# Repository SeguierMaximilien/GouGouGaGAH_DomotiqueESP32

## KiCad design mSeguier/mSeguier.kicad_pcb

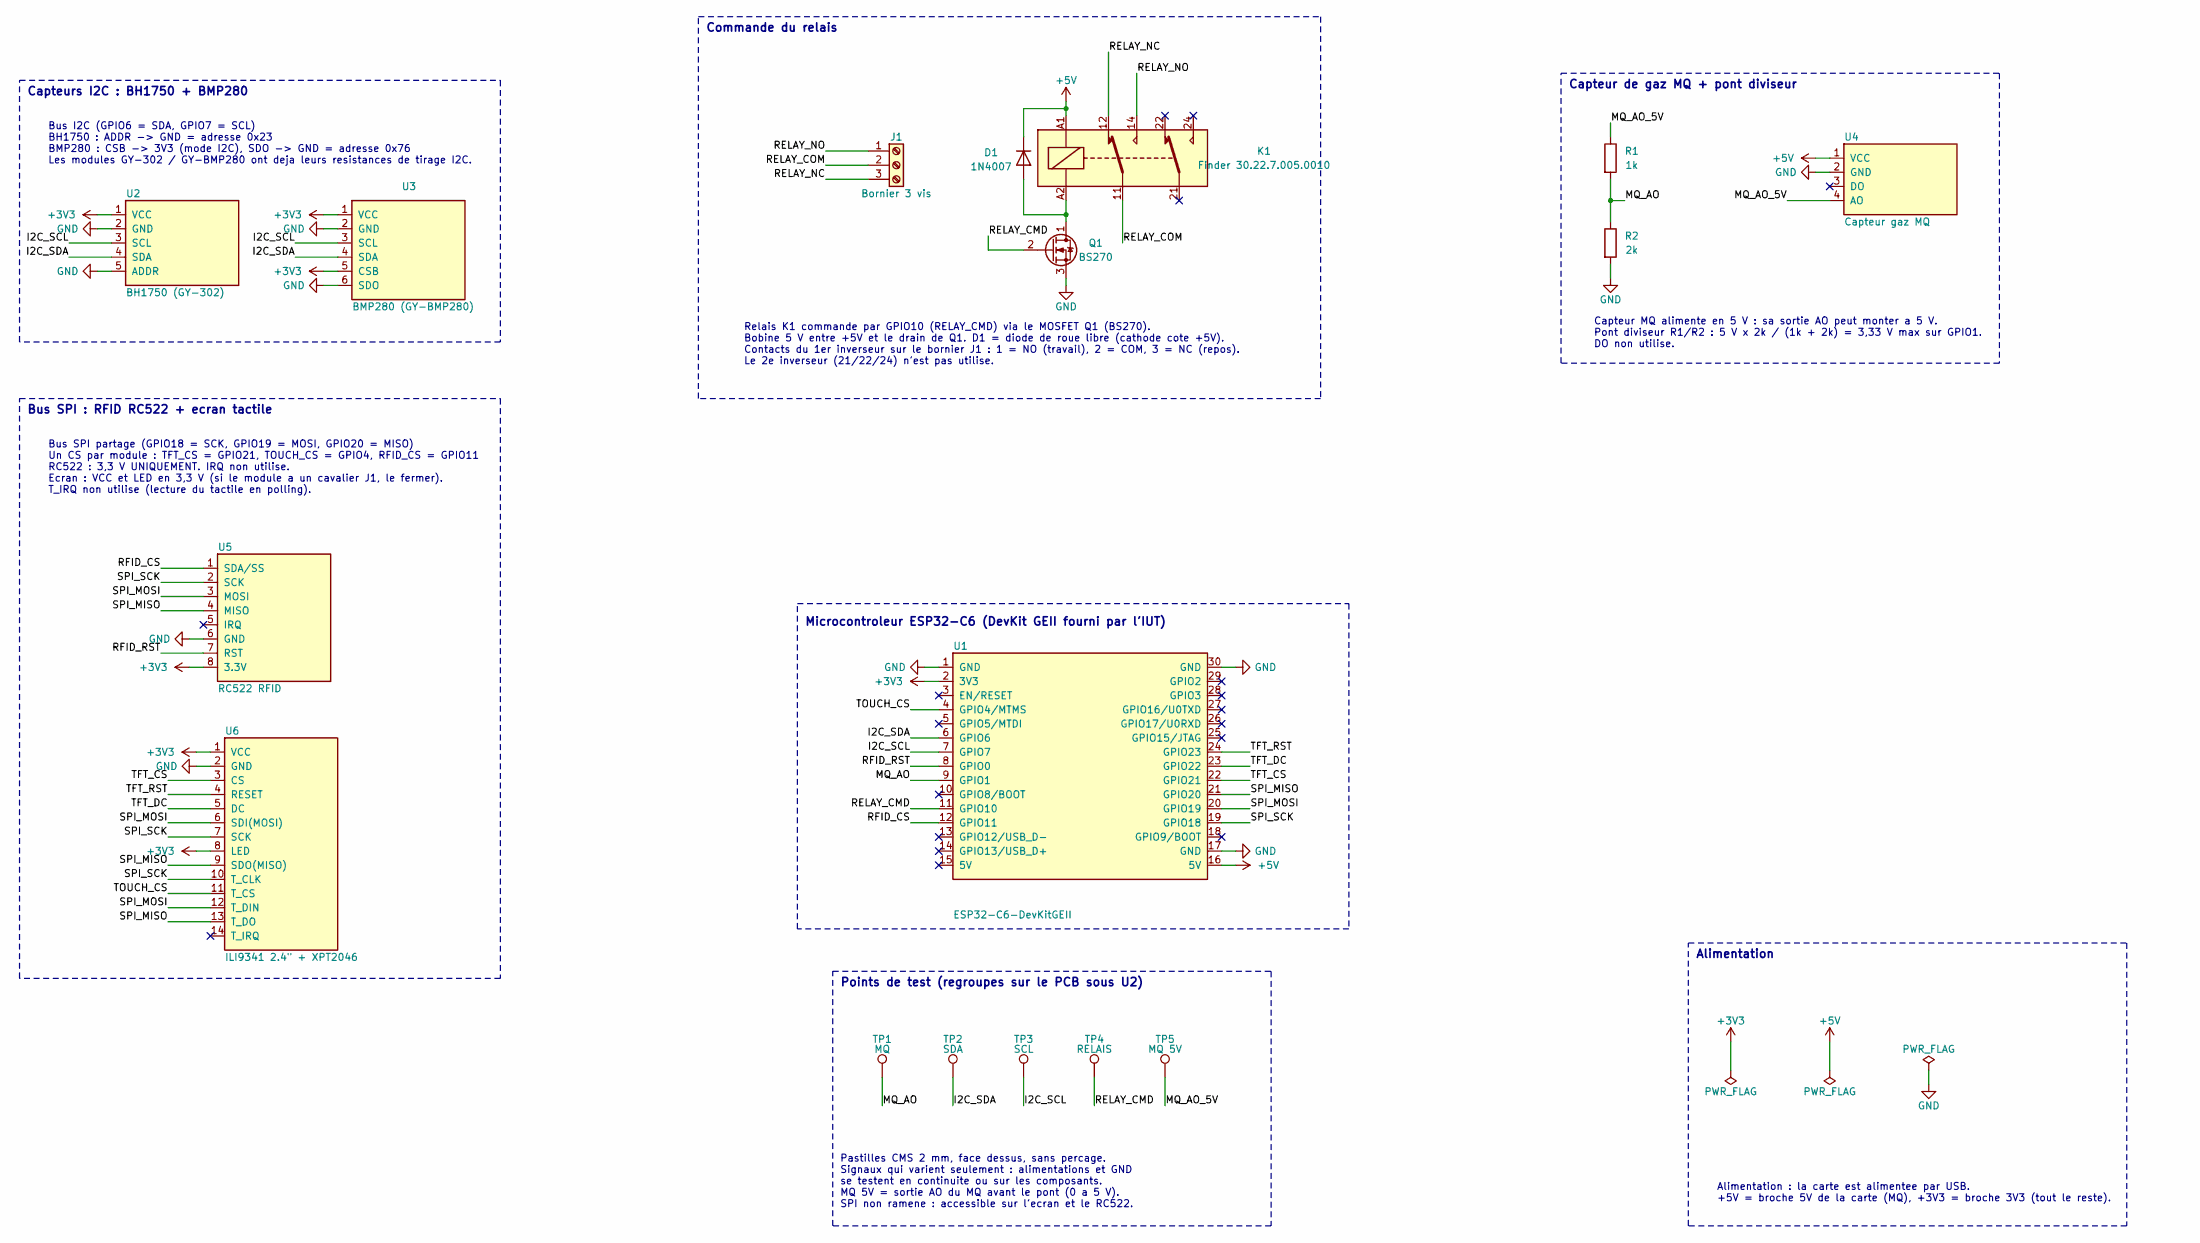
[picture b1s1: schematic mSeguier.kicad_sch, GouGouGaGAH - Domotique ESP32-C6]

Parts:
D1: 1N4007; D_DO-41_SOD81_P10.16mm_Horizontal
J1: Bornier 3 vis; TerminalBlock_Phoenix_MKDS-1,5-3_1x03_P5.00mm_Horizontal
K1: Finder 30.22.7.005.0010; Relay_DPDT_Finder_30.22
Q1: BS270; TO-92_Inline_Wide
R1: 1k; R_Axial_DIN0207_L6.3mm_D2.5mm_P10.16mm_Horizontal
R2: 2k; R_Axial_DIN0207_L6.3mm_D2.5mm_P10.16mm_Horizontal
TP1: MQ; TestPoint_Pad_D2.0mm
TP2: SDA; TestPoint_Pad_D2.0mm
TP3: SCL; TestPoint_Pad_D2.0mm
TP4: RELAIS; TestPoint_Pad_D2.0mm
TP5: MQ 5V; TestPoint_Pad_D2.0mm
U1: ESP32-C6-DevKitGEII
U2: BH1750 (GY-302); BH1750_GY-302
U3: BMP280 (GY-BMP280); BMP280_GY-BMP280-3.3
U4: Capteur gaz MQ; MQ_Gas_Sensor_Module_FlyingFish
U5: RC522 RFID; RFID_RC522_Module
U6: ILI9341 2.4" + XPT2046; TFT_2.4in_SPI_ILI9341_MSP2402

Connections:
+3V3: U1.2 (3V3), U2.1 (VCC), U3.1 (VCC), U3.5 (CSB), U5.8 (3.3V), U6.1 (VCC), U6.8 (LED)
+5V: D1.1 (K), K1.A1, U1.16 (5V), U4.1 (VCC)
/I2C_SCL: TP3.1, U1.7 (GPIO7), U2.3 (SCL), U3.3 (SCL)
/I2C_SDA: TP2.1, U1.6 (GPIO6), U2.4 (SDA), U3.4 (SDA)
/MQ_AO: R1.2, R2.1, TP1.1, U1.9 (GPIO1)
/MQ_AO_5V: R1.1, TP5.1, U4.4 (AO)
/RELAY_CMD: Q1.2 (G), TP4.1, U1.11 (GPIO10)
/RELAY_COM: J1.2, K1.11
/RELAY_NC: J1.3, K1.12
/RELAY_NO: J1.1, K1.14
/RFID_CS: U1.12 (GPIO11), U5.1 (SDA/SS)
/RFID_RST: U1.8 (GPIO0), U5.7 (RST)
/SPI_MISO: U1.21 (GPIO20), U5.4 (MISO), U6.9 (SDO(MISO)), U6.13 (T_DO)
/SPI_MOSI: U1.20 (GPIO19), U5.3 (MOSI), U6.6 (SDI(MOSI)), U6.12 (T_DIN)
/SPI_SCK: U1.19 (GPIO18), U5.2 (SCK), U6.7 (SCK), U6.10 (T_CLK)
/TFT_CS: U1.22 (GPIO21), U6.3 (CS)
/TFT_DC: U1.23 (GPIO22), U6.5 (DC)
/TFT_RST: U1.24 (GPIO23), U6.4 (RESET)
/TOUCH_CS: U1.4 (GPIO4/MTMS), U6.11 (T_CS)
GND: Q1.3 (S), R2.2, U1.1 (GND), U1.17 (GND), U1.30 (GND), U2.2 (GND), U2.5 (ADDR), U3.2 (GND), U3.6 (SDO), U4.2 (GND), U5.6 (GND), U6.2 (GND)
unnamed: D1.2 (A), K1.A2, Q1.1 (D)

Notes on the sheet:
Capteur de gaz MQ + pont diviseur
Bus SPI : RFID RC522 + ecran tactile
Bus SPI partage (GPIO18 = SCK, GPIO19 = MOSI, GPIO20 = MISO) Un CS par module : TFT_CS = GPIO21, TOUCH_CS = GPIO4, RFID_CS = GPIO11 RC522 : 3,3 V UNIQUEMENT. IRQ non utilise. Ecran : VCC et LED en 3,3 V (si le module a un cavalier J1, le fermer). T_IRQ non utilise (lecture du tactile en polling).
Capteurs I2C : BH1750 + BMP280
Commande du relais
Alimentation
Relais K1 commande par GPIO10 (RELAY_CMD) via le MOSFET Q1 (BS270). Bobine 5 V entre +5V et le drain de Q1. D1 = diode de roue libre (cathode cote +5V). Contacts du 1er inverseur sur le bornier J1 : 1 = NO (travail), 2 = COM, 3 = NC (repos). Le 2e inverseur (21/22/24) n'est pas utilise.
Alimentation : la carte est alimentee par USB. +5V = broche 5V de la carte (MQ), +3V3 = broche 3V3 (tout le reste).
Microcontroleur ESP32-C6 (DevKit GEII fourni par l'IUT)
Capteur MQ alimente en 5 V : sa sortie AO peut monter a 5 V. Pont diviseur R1/R2 : 5 V x 2k / (1k + 2k) = 3,33 V max sur GPIO1. DO non utilise.
Bus I2C (GPIO6 = SDA, GPIO7 = SCL) BH1750 : ADDR -> GND = adresse 0x23 BMP280 : CSB -> 3V3 (mode I2C), SDO -> GND = adresse 0x76 Les modules GY-302 / GY-BMP280 ont deja leurs resistances de tirage I2C.
Points de test (regroupes sur le PCB sous U2)
Pastilles CMS 2 mm, face dessus, sans percage. Signaux qui varient seulement : alimentations et GND se testent en continuite ou sur les composants. MQ 5V = sortie AO du MQ avant le pont (0 a 5 V). SPI non ramene : accessible sur l'ecran et le RC522.

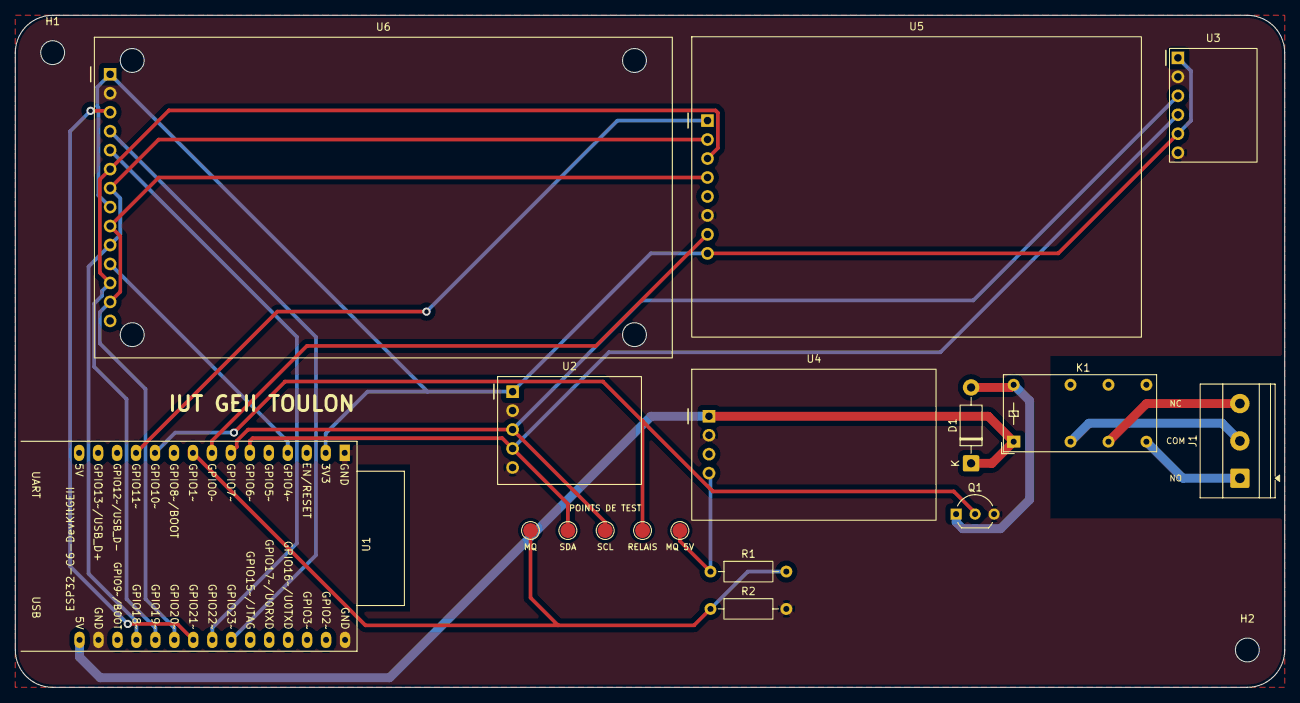
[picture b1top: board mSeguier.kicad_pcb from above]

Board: 2 copper layers, 170.0 x 90.0 mm, 19 parts (0 on the bottom side), 21 nets.

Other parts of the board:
H1, H2: M3; MountingHole_3.2mm_M3

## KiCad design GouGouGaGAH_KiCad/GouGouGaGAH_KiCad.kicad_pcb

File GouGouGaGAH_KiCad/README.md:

# GouGouGaGAH_KiCad : schéma du projet domotique

Sous-projet KiCad du montage ESP32-C6. Le schéma reprend exactement le brochage de
`GouGouGaGAH_DomotiqueESP32/include/pinout.h`.

## Ouvrir le projet

1. Ouvre `GouGouGaGAH_KiCad.kicad_pro` avec KiCad (version 8, 9 ou 10).
2. Ouvre le schéma : tout est déjà relié et chaque composant a son empreinte.
3. Le circuit imprimé (`GouGouGaGAH_KiCad.kicad_pcb`) est placé et routé (voir plus bas).
   Si tu modifies le schéma, mets le PCB à jour avec *Outils > Mettre à jour le PCB depuis le
   schéma* (touche F8).

Le dossier contient sa propre bibliothèque, déclarée dans les tables du projet :

| Fichier | Contenu |
|---|---|
| `GouGouGaGAH.kicad_sym` | Symboles de la carte nanoESP32-C6 et des 5 modules (plus la DevKitC-1 en réserve) |
| `../Kad_Lib/ESP32_C6_modules.pretty/` | Tes empreintes : carte et 5 modules |
| `GouGouGaGAH.pretty/` | Empreinte ESP32-C6-DevKitC-1 (en réserve, non utilisée) |
| `sym-lib-table`, `fp-lib-table` | Déclarent ces bibliothèques pour ce projet uniquement |

Les résistances et condensateurs utilisent les bibliothèques standard de KiCad.
Garde le dossier `Kad_Lib` à côté de `GouGouGaGAH_KiCad`, le chemin est relatif.

## Circuit imprimé

- Carte double face de 165 × 114 mm, aperçus dans `rendu_pcb.png` (dessus) et `rendu_pcb_dessous.png`.
- GND : aucune piste, tout passe par un plan de masse sur les deux faces (rayons thermiques
  pour faciliter la soudure, liaison pleine sur U2 broche 2 et Q1 broche 3).
- Haut : écran (gauche) et RC522 (droite). Milieu : nanoESP32-C6 avec l'USB-C au bord gauche,
  BH1750 et BMP280 à côté. Bas : capteur MQ, pont R1/R2/C1, condensateurs C2/C3.
  À droite : relais, MOSFET, diode et bornier au bord de la carte.
- Les modules s'enfichent sur des barrettes : des pistes passent sous les modules, c'est normal.
  Aucune piste sous l'antenne de la nanoESP32-C6 (zone interdite de l'empreinte).
- Largeurs : 0,3 mm pour les signaux, 0,8 mm pour +5V / +3V3 / bobine du relais,
  1,5 mm pour les contacts du relais. Isolement 0,2 mm (0,5 mm pour les contacts du relais).
- Contrôle KiCad (DRC) : 0 erreur, 0 avertissement, 0 liaison manquante, PCB conforme au schéma.
- Si tu modifies des pistes, refais le remplissage des plans avec la touche B.
- **Attention** : les contacts du relais ne sont pas isolés pour du 230 V (il faudrait
  plusieurs millimètres d'écart et une fente). Ne commute que de la basse tension avec cette carte.

## Liaisons

| Réseau | ESP32-C6 | Relié à |
|---|---|---|
| I2C_SDA | GPIO6 | BH1750 SDA, BMP280 SDA |
| I2C_SCL | GPIO7 | BH1750 SCL, BMP280 SCL |
| SPI_SCK | GPIO18 | RC522 SCK, écran SCK, tactile T_CLK |
| SPI_MOSI | GPIO19 | RC522 MOSI, écran SDI, tactile T_DIN |
| SPI_MISO | GPIO20 | RC522 MISO, écran SDO, tactile T_DO |
| TFT_CS | GPIO21 | écran CS |
| TFT_DC | GPIO22 | écran DC |
| TFT_RST | GPIO23 | écran RESET |
| TOUCH_CS | GPIO4 | tactile T_CS |
| RFID_CS | GPIO11 | RC522 SDA/SS |
| RFID_RST | GPIO0 | RC522 RST |
| MQ_AO | GPIO1 | point milieu du pont R1/R2 (+ C1) |
| MQ_AO_5V | - | sortie AO du capteur MQ, entrée du pont R1/R2 |
| RELAY_CMD | GPIO10 | grille du MOSFET Q1 |
| RELAY_COIL | - | drain de Q1, bobine A2 du relais, anode de D1 |
| RELAY_NO / COM / NC | - | contacts 14 / 11 / 12 du relais, vers le bornier J1 (1 / 2 / 3) |
| +5V | broches 5V | capteur MQ (VCC), bobine A1 du relais, cathode de D1 |
| +3V3 | broche 3V3 | BH1750, BMP280 (VCC + CSB), RC522, écran (VCC + LED) |
| GND | GND | tout le monde, plus BH1750 ADDR et BMP280 SDO |

Broches non utilisées (croix « non connecté ») : MQ DO, RC522 IRQ, écran T_IRQ, et les GPIO libres de la carte.

## Composants et empreintes

| Réf. | Composant | Empreinte |
|---|---|---|
| U1 | MuseLab nanoESP32-C6 (2 x 15 broches) | `ESP32_C6_modules:MuseLab_nanoESP32-C6` |
| U2 | BH1750 (GY-302) | `ESP32_C6_modules:BH1750_GY-302` |
| U3 | BMP280 (GY-BMP280) | `ESP32_C6_modules:BMP280_GY-BMP280-3.3` |
| U4 | Capteur gaz MQ | `ESP32_C6_modules:MQ_Gas_Sensor_Module_FlyingFish` |
| U5 | RC522 | `ESP32_C6_modules:RFID_RC522_Module` |
| U6 | Écran ILI9341 2.4" + XPT2046 (MSP2402) | `ESP32_C6_modules:TFT_2.4in_SPI_ILI9341_MSP2402` |
| R1 | 1 kΩ | `Resistor_THT:R_Axial_DIN0207_L6.3mm_D2.5mm_P10.16mm_Horizontal` |
| R2 | 2 kΩ | `Resistor_THT:R_Axial_DIN0207_L6.3mm_D2.5mm_P10.16mm_Horizontal` |
| C1 | 100 nF | `Capacitor_THT:C_Disc_D5.0mm_W2.5mm_P5.00mm` |
| C2 | 10 µF (sur +3V3) | `Capacitor_THT:CP_Radial_D5.0mm_P2.00mm` |
| C3 | 10 µF (sur +5V) | `Capacitor_THT:CP_Radial_D5.0mm_P2.00mm` |
| Q1 | MOSFET BS270 (symbole BS170, même brochage D-G-S) | `Package_TO_SOT_THT:TO-92_Inline` |
| K1 | Relais Finder 30.22.7.005 (2 inverseurs, bobine 5 V) | `Relay_THT:Relay_DPDT_Finder_30.22` |
| D1 | Diode de roue libre 1N4007 | `Diode_THT:D_DO-41_SOD81_P10.16mm_Horizontal` |
| J1 | Bornier à vis 3 points, pas de 5 mm | `TerminalBlock_Phoenix:TerminalBlock_Phoenix_MKDS-1,5-3_1x03_P5.00mm_Horizontal` |

L'ordre des broches des symboles est identique à celui de tes empreintes (vérifié broche par broche).
Sur l'empreinte de la nanoESP32-C6, les textes de sérigraphie des broches 7 à 15 et 22 à 30 sont
décalés par rapport aux pastilles : la numérotation reste juste, c'est seulement l'affichage.

## Points d'attention

- **Capteur MQ** : alimenté en 5 V, sa sortie AO peut monter à 5 V alors que l'ESP32 n'accepte
  que 3,3 V. Le pont R1 (1 kΩ) / R2 (2 kΩ) ramène 5 V à 3,33 V au maximum.
- **RC522** : 3,3 V uniquement, jamais 5 V.
- **Écran** : VCC et LED sont en 3,3 V. Si ton module a un cavalier J1 à côté du régulateur,
  ferme-le pour qu'il fonctionne correctement en 3,3 V.
- **TOUCH_CS sur GPIO4** : GPIO4 est une broche de configuration au démarrage (MTMS), mais elle
  ne sert qu'au choix de l'interface JTAG, réglage désactivé par défaut. Aucun problème ici.
- **Bibliothèque Espressif** : son symbole ESP32-C6-DevKitC-1 oublie la broche 32 (GND) qui
  existe pourtant sur l'empreinte. Le symbole du projet la corrige.
- **Relais** : piloté par GPIO10 (libre dans `pinout.h`, à y ajouter : `#define RELAY_CMD 10`).
  Le BS270 commence à conduire vers 2,5 V au maximum : en 3,3 V ça marche, mais c'est un peu juste.
- **À vérifier sur tes composants** : la diode (corps noir = 1N4007, verre orange = 1N4148,
  empreinte `Diode_THT:D_DO-35_SOD27_P10.16mm_Horizontal`), le pas du bornier (5 mm ou 3,5 mm)
  et l'ordre des pattes du BS270 (D-G-S, méplat face à soi) au multimètre.

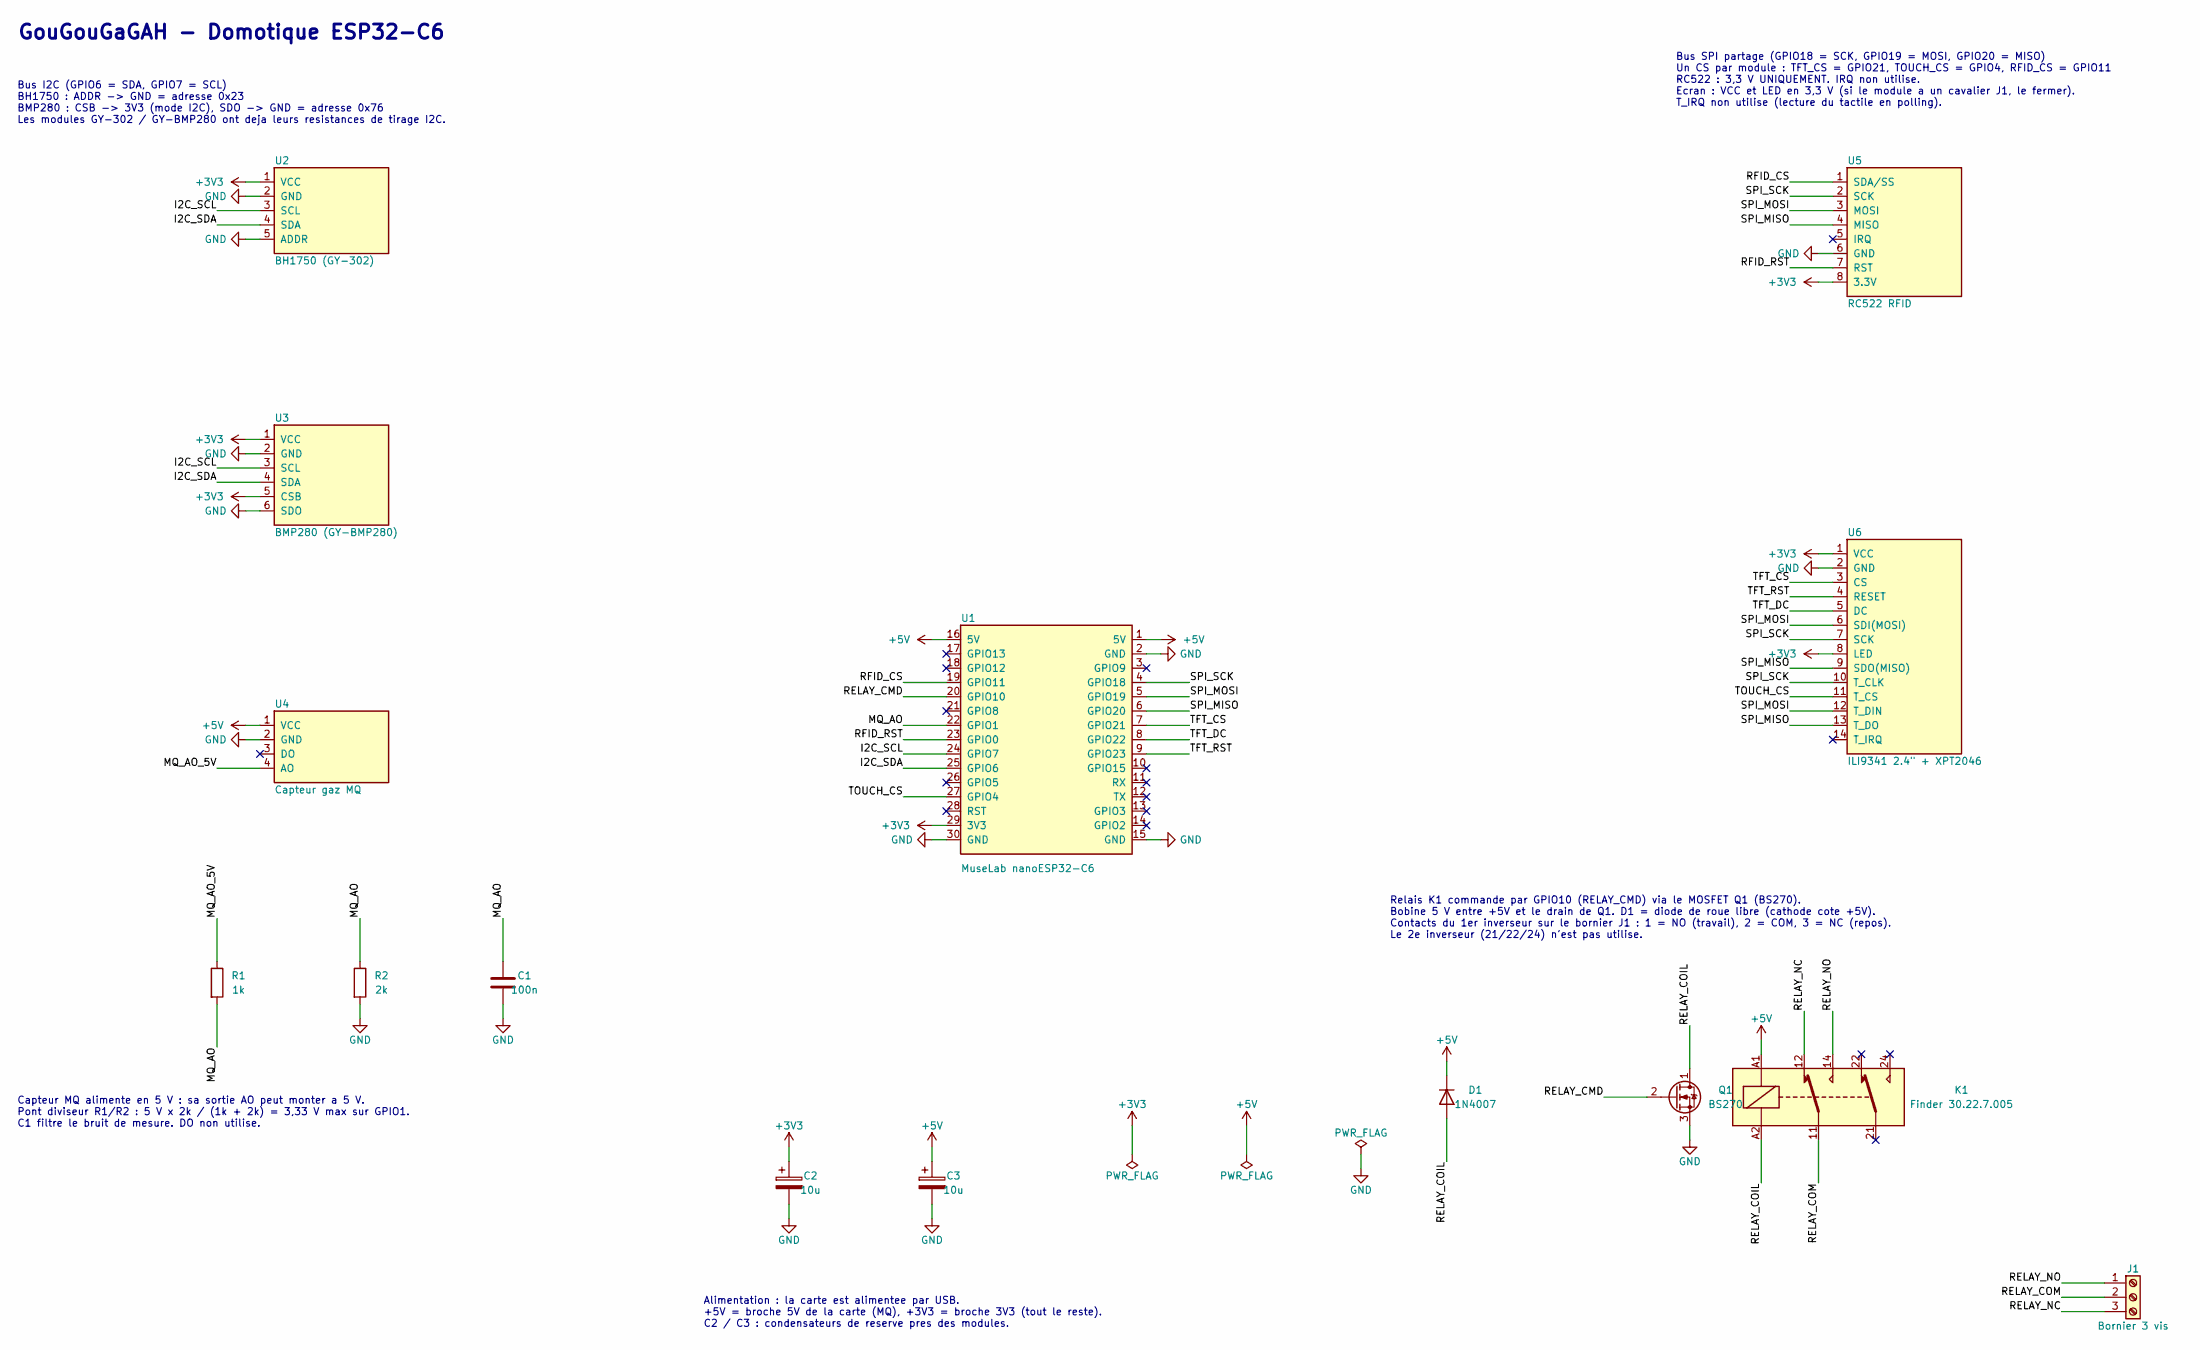
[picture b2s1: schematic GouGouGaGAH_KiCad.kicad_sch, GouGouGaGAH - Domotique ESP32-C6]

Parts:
C1: 100n; C_Disc_D5.0mm_W2.5mm_P5.00mm
C2, C3: 10u; CP_Radial_D5.0mm_P2.00mm
D1: 1N4007; D_DO-41_SOD81_P10.16mm_Horizontal
J1: Bornier 3 vis; TerminalBlock_Phoenix_MKDS-1,5-3_1x03_P5.00mm_Horizontal
K1: Finder 30.22.7.005; Relay_DPDT_Finder_30.22
Q1: BS270; TO-92_Inline
R1: 1k; R_Axial_DIN0207_L6.3mm_D2.5mm_P10.16mm_Horizontal
R2: 2k; R_Axial_DIN0207_L6.3mm_D2.5mm_P10.16mm_Horizontal
U1: MuseLab nanoESP32-C6; MuseLab_nanoESP32-C6
U2: BH1750 (GY-302); BH1750_GY-302
U3: BMP280 (GY-BMP280); BMP280_GY-BMP280-3.3
U4: Capteur gaz MQ; MQ_Gas_Sensor_Module_FlyingFish
U5: RC522 RFID; RFID_RC522_Module
U6: ILI9341 2.4" + XPT2046; TFT_2.4in_SPI_ILI9341_MSP2402

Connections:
+3V3: C2.1, U1.29 (3V3), U2.1 (VCC), U3.1 (VCC), U3.5 (CSB), U5.8 (3.3V), U6.1 (VCC), U6.8 (LED)
+5V: C3.1, D1.1 (K), K1.A1, U1.1 (5V), U1.16 (5V), U4.1 (VCC)
/I2C_SCL: U1.24 (GPIO7), U2.3 (SCL), U3.3 (SCL)
/I2C_SDA: U1.25 (GPIO6), U2.4 (SDA), U3.4 (SDA)
/MQ_AO: C1.1, R1.2, R2.1, U1.22 (GPIO1)
/MQ_AO_5V: R1.1, U4.4 (AO)
/RELAY_CMD: Q1.2 (G), U1.20 (GPIO10)
/RELAY_COIL: D1.2 (A), K1.A2, Q1.1 (D)
/RELAY_COM: J1.2, K1.11
/RELAY_NC: J1.3, K1.12
/RELAY_NO: J1.1, K1.14
/RFID_CS: U1.19 (GPIO11), U5.1 (SDA/SS)
/RFID_RST: U1.23 (GPIO0), U5.7 (RST)
/SPI_MISO: U1.6 (GPIO20), U5.4 (MISO), U6.9 (SDO(MISO)), U6.13 (T_DO)
/SPI_MOSI: U1.5 (GPIO19), U5.3 (MOSI), U6.6 (SDI(MOSI)), U6.12 (T_DIN)
/SPI_SCK: U1.4 (GPIO18), U5.2 (SCK), U6.7 (SCK), U6.10 (T_CLK)
/TFT_CS: U1.7 (GPIO21), U6.3 (CS)
/TFT_DC: U1.8 (GPIO22), U6.5 (DC)
/TFT_RST: U1.9 (GPIO23), U6.4 (RESET)
/TOUCH_CS: U1.27 (GPIO4), U6.11 (T_CS)
GND: C1.2, C2.2, C3.2, Q1.3 (S), R2.2, U1.2 (GND), U1.15 (GND), U1.30 (GND), U2.2 (GND), U2.5 (ADDR), U3.2 (GND), U3.6 (SDO), U4.2 (GND), U5.6 (GND), U6.2 (GND)

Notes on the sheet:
Relais K1 commande par GPIO10 (RELAY_CMD) via le MOSFET Q1 (BS270). Bobine 5 V entre +5V et le drain de Q1. D1 = diode de roue libre (cathode cote +5V). Contacts du 1er inverseur sur le bornier J1 : 1 = NO (travail), 2 = COM, 3 = NC (repos). Le 2e inverseur (21/22/24) n'est pas utilise.
GouGouGaGAH - Domotique ESP32-C6
Bus I2C (GPIO6 = SDA, GPIO7 = SCL) BH1750 : ADDR -> GND = adresse 0x23 BMP280 : CSB -> 3V3 (mode I2C), SDO -> GND = adresse 0x76 Les modules GY-302 / GY-BMP280 ont deja leurs resistances de tirage I2C.
Capteur MQ alimente en 5 V : sa sortie AO peut monter a 5 V. Pont diviseur R1/R2 : 5 V x 2k / (1k + 2k) = 3,33 V max sur GPIO1. C1 filtre le bruit de mesure. DO non utilise.
Bus SPI partage (GPIO18 = SCK, GPIO19 = MOSI, GPIO20 = MISO) Un CS par module : TFT_CS = GPIO21, TOUCH_CS = GPIO4, RFID_CS = GPIO11 RC522 : 3,3 V UNIQUEMENT. IRQ non utilise. Ecran : VCC et LED en 3,3 V (si le module a un cavalier J1, le fermer). T_IRQ non utilise (lecture du tactile en polling).
Alimentation : la carte est alimentee par USB. +5V = broche 5V de la carte (MQ), +3V3 = broche 3V3 (tout le reste). C2 / C3 : condensateurs de reserve pres des modules.

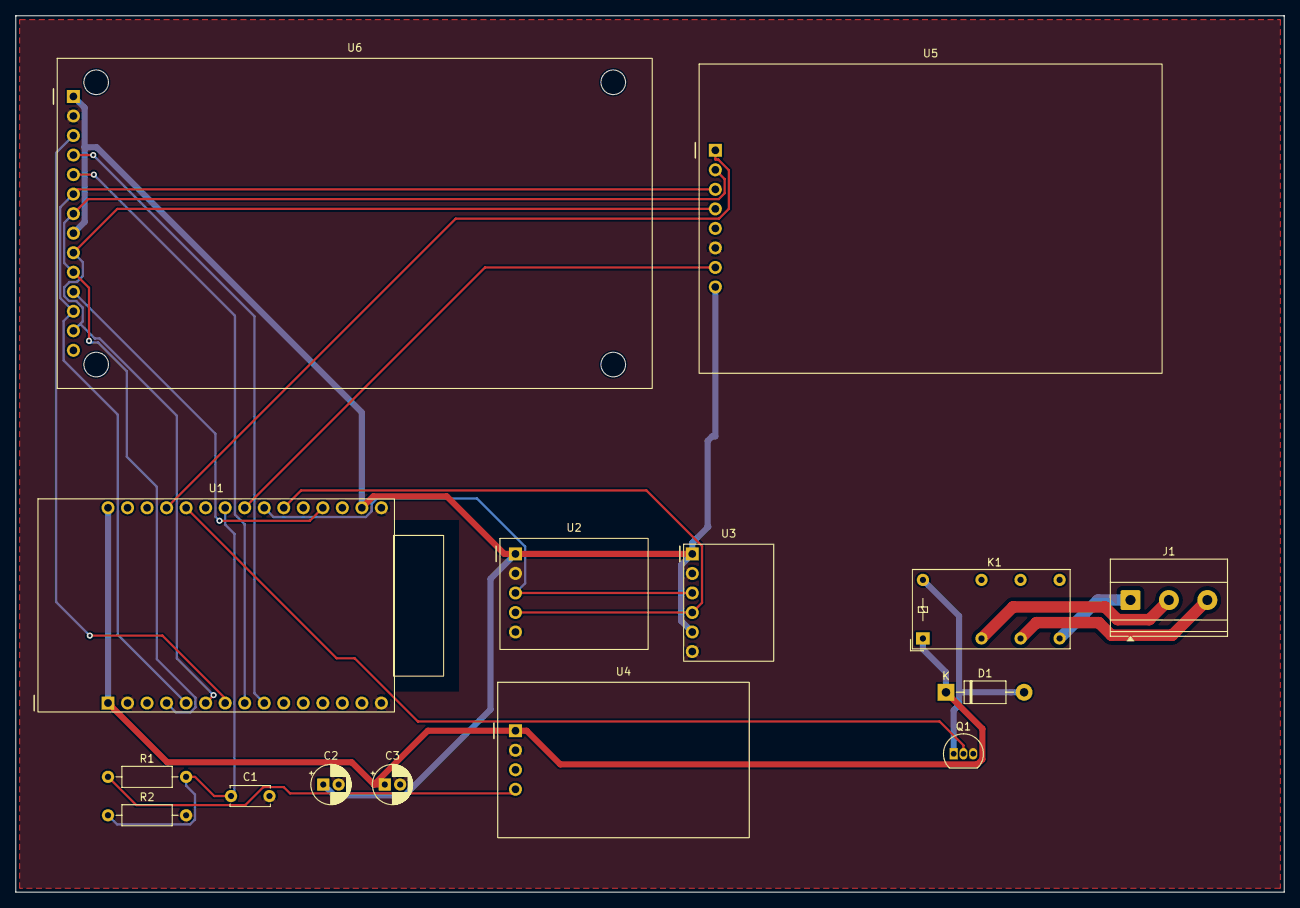
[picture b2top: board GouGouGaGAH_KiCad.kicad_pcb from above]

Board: 2 copper layers, 165.0 x 114.0 mm, 15 parts (0 on the bottom side), 21 nets.

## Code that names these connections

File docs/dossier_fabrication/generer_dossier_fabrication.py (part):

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
def partie_procedure():
    pm = table(["Point", "Signal", "Emplacement", "Valeur attendue"], [
        ["TP1", "MQ (MQ_AO)", "Bloc « POINTS DE TEST »", "Entrée GPIO1 après le pont R1/R2, 0 à 3,33 V"],
        ["TP2", "SDA (I2C_SDA)", "Bloc « POINTS DE TEST »", "Données I2C, GPIO6, 0 / 3,3 V"],
        ["TP3", "SCL (I2C_SCL)", "Bloc « POINTS DE TEST »", "Horloge I2C, GPIO7, 0 / 3,3 V, 100 kHz"],
        ["TP4", "RELAIS (RELAY_CMD)", "Bloc « POINTS DE TEST »", "Grille de Q1, GPIO10 : 0 V repos, 3,3 V travail"],
        ["TP5", "MQ 5V (MQ_AO_5V)", "Bloc « POINTS DE TEST »", "Sortie AO du capteur MQ avant le pont, 0 à 5 V"],
        ["+5V", "Alimentation 5 V", "U4 broche 1 (VCC) ou U1 broche 16", "4,75 à 5,25 V"],
        ["+3V3", "Alimentation 3,3 V", "U2 broche 1 (VCC) ou U1 broche 2", "3,14 à 3,47 V"],
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         "Niveau haut 3,3 V sur TP2 et TP3 ; continuité U1 broches 6 et 7 vers U2 et U3 ; +3V3 sur U2 broche 1"],
        ["Un seul capteur I2C en échec", "Soudure du module, broche d'adresse",
         "Reprendre les soudures ; ADDR de U2 et SDO de U3 reliés à GND (adresses 0x23 et 0x76)"],
        ["« [RC522] ECHEC »", "SPI, RFID_CS (GPIO11), RFID_RST (GPIO0) ou alimentation",
         "Continuité des broches 1, 2, 3, 4 et 7 de U5 ; 3,3 V sur U5 broche 8 (jamais 5 V)"],
        ["Écran blanc ou noir", "TFT_CS (GPIO21), TFT_DC (GPIO22), TFT_RST (GPIO23), SPI",
         "Continuité des broches 3, 4, 5, 6 et 7 de U6 ; rétroéclairage (U6 broche 8) à 3,3 V"],
        ["Tactile sans réaction", "TOUCH_CS (GPIO4) ou bus SPI", "Continuité U1 broche 4 – U6 broche 11 et broches 10, 12, 13 de U6"],
        ["Valeur MQ bloquée à 0", "MQ non alimenté, R1 coupée ou TP1 en court-circuit",
         "+5V sur U4 broche 1 ; tension TP5 ; continuité de R1"],
        ["Valeur MQ bloquée à 4095", "R2 coupée : TP1 égal à TP5 (jusqu'à 5 V sur GPIO1)",
         "Couper l'alimentation immédiatement (risque pour l'ESP32) ; contrôler et remplacer R2"],
        ["Relais inactif, TP4 à 3,3 V", "Q1, bobine, D1 ou +5V", "Tension A1-A2 (test 4.8) ; brochage de Q1 ; résistance de bobine (test 2.3)"],
        ["Relais inactif, TP4 à 0 V", "GPIO10 ou programme", "Continuité U1 broche 11 – TP4 – Q1 grille ; message « [Relais] ON » sur le moniteur série"],
        ["Échauffement de Q1 ou de D1 au travail", "D1 montée à l'envers (court-circuit du +5V par Q1)",
         "Couper l'alimentation ; contrôler l'orientation de D1 (bague côté +5V)"],
        ["Contacts du bornier sans effet", "Soudure de K1 ou J1, contacts usés", "Continuité COM-NO et COM-NC (tests 2.5 et 4.8)"],
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consignés sur la fiche d'intervention.</p>
<div style="font-size:9.5pt">{N.tableau(diag, "Guide de diagnostic des défauts courants")}</div>
<p>Limite connue : la grille de Q1 n'a pas de résistance de rappel à la masse. Pendant le démarrage de l'ESP32,
avant l'exécution de <span class="mono">relais_setup()</span>, GPIO10 est en haute impédance et le relais peut
coller brièvement. Ce comportement n'est pas un défaut de fabrication ; une résistance de 100 kΩ entre grille
et source le supprimerait dans une révision de la carte.</p>
"""
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
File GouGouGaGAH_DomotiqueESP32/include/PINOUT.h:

#ifndef PINOUT_H
#define PINOUT_H

// ========================================================
// PINOUT - ESP32-C6-WROOM
// ========================================================

// ---- Bus I2C (BH1750 + BMP280) ----
#define I2C_SDA     6
#define I2C_SCL     7

// ---- Bus SPI partagé (TFT + Tactile + RC522) ----
#define SPI_SCK     18
#define SPI_MOSI    19
#define SPI_MISO    20

// ---- Ecran TFT ----
#define TFT_CS      21
#define TFT_DC      22
#define TFT_RST     23
// LED (retroeclairage) -> 3V3 direct, pas de GPIO

// ---- Tactile (partage SPI_SCK / SPI_MOSI / SPI_MISO) ----
#define TOUCH_CS    4

// ---- RFID RC522 (partage SPI_SCK / SPI_MOSI / SPI_MISO) ----
#define RFID_CS     11
#define RFID_RST    0

// ---- Capteur MQ (analogique) ----
#define MQ_AO       1

// ---- Relais (via transistor, actif a l'etat haut) ----
#define RELAIS_PIN  10

#endif // PINOUT_H

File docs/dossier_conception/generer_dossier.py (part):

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    e.append(fleche([(460, 388), (540, 388)], "SPI 18/19/20\nCS 21, 4, 11\nRST 23, 0", 500, 352, double=True))
    e.append(fleche([(790, 100), (880, 100)], "WiFi\nMQTT", 835, 84, double=True))
    e.append(fleche([(790, 225), (880, 225)], "HTTP\nTempo", 835, 209, double=True))
    e.append(fleche([(790, 365), (880, 365)], "RELAY_CMD\nGPIO10", 835, 349))
    e.append(fleche([(995, 430), (995, 470)], "contacts", 1003, 455, ancre="start"))
    e.append(fleche([(720, 455), (720, 595), (880, 595)], "PWM GPIO2", 770, 588))
    e.append(fleche([(995, 160), (995, 185)], "", double=True, couleur="#8a94a6"))
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<td>Mesure l'éclairement (lx), la température (°C) et la pression (hPa). Bus I2C partagé, adresses 0x23 et 0x76.</td></tr>
<tr><td>FP3 Détecter le gaz</td><td>Module MQ (U4), R1 1 kΩ, R2 2 kΩ</td>
<td>Donne une tension image de la concentration de gaz. Le pont diviseur ramène la sortie 0-5 V à 0-3,33 V
pour l'entrée analogique GPIO1.</td></tr>
<tr><td>FP4 Dialoguer avec l'habitant</td><td>Écran TFT 2,4" ILI9341 + XPT2046 (U6), RC522 (U5)</td>
<td>Affiche les mesures et les menus, reçoit les appuis tactiles, lit l'identifiant des badges. Bus SPI partagé,
un chip select par module.</td></tr>
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<td>Exécute le programme : contrôle d'accès, menus, mémoire des badges en NVS, MQTT vers Home Assistant,
lecture de la couleur Tempo, LED RGB, sortie PWM.</td></tr>
<tr><td>FP6 Commander la gâche</td><td>BS270 (Q1), D1, relais Finder 30.22.7.005 (K1), bornier J1</td>
<td>Le MOSFET commute la bobine 5 V du relais depuis GPIO10. D1 protège Q1 de la surtension à la coupure.
Les contacts NO/COM/NC sortent sur J1 vers la gâche.</td></tr>
</table>
<h2>Liaisons entre fonctions</h2>
<table>
<tr><th style="width:24%">Liaison</th><th style="width:22%">Nature</th><th>Signaux (GPIO de l'ESP32-C6)</th></tr>
<tr><td>FP2 → FP5</td><td>numérique, I2C</td><td>SDA = GPIO6, SCL = GPIO7</td></tr>
<tr><td>FP3 → FP5</td><td>analogique</td><td>MQ_AO divisé, 0 à 3,33 V sur GPIO1 (ADC 12 bits)</td></tr>
<tr><td>FP4 ↔ FP5</td><td>numérique, SPI</td><td>SCK = GPIO18, MOSI = GPIO19, MISO = GPIO20 ; TFT_CS = 21, TFT_DC = 22, TFT_RST = 23,
TOUCH_CS = 4, RFID_CS = 11, RFID_RST = 0</td></tr>
<tr><td>FP5 → FP6</td><td>logique TOR</td><td>RELAY_CMD = GPIO10, actif à l'état haut</td></tr>
<tr><td>FP5 → éclairage / VMC</td><td>PWM</td><td>GPIO2, rapport cyclique 0 à 100 %</td></tr>
<tr><td>FP5 → LED RGB</td><td>série WS2812</td><td>GPIO8 (LED intégrée à la carte)</td></tr>
<tr><td>FP5 ↔ Home Assistant</td><td>WiFi 2,4 GHz, MQTT</td><td>topics <code>gougougagah/…</code> (voir annexe B)</td></tr>
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<tr><td>R1, R2</td><td>Résistances 1 kΩ et 2 kΩ</td><td>FP3</td><td>5 V × 2k / (1k + 2k) = 3,33 V max</td></tr>
<tr><td>U5</td><td>Module RFID RC522</td><td>FP4</td><td>Alimenté en 3,3 V uniquement</td></tr>
<tr><td>U6</td><td>Écran TFT 2,4" ILI9341 + tactile XPT2046 (MSP2402)</td><td>FP4</td><td>Rétroéclairage sur 3V3</td></tr>
<tr><td>Q1</td><td>MOSFET canal N BS270</td><td>FP6</td><td>Commande de la bobine depuis GPIO10</td></tr>
<tr><td>D1</td><td>Diode 1N4004</td><td>FP6</td><td>Roue libre, cathode côté +5V</td></tr>
<tr><td>K1</td><td>Relais Finder 30.22.7.005.0010, 2RT, bobine 5 V</td><td>FP6</td><td>1er inverseur utilisé</td></tr>
<tr><td>J1</td><td>Bornier à vis 3 points</td><td>FP6</td><td>1 = NO, 2 = COM, 3 = NC</td></tr>
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<h2>Dimensionnement de la commande du relais</h2>
<p>La bobine 5 V du relais Finder 30.22 consomme environ 40 mA (résistance d'environ 125 Ω).
Une sortie de l'ESP32-C6 ne peut pas fournir ce courant sous 5 V : le MOSFET BS270 (V<sub>GS(th)</sub> inférieure à 2,5 V,
I<sub>D</sub> max 400 mA) est commandé directement en 3,3 V par GPIO10 et commute la bobine côté masse.
La diode D1 en parallèle sur la bobine écoule le courant de self à l'ouverture et protège Q1.</p>
"""

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        "module_tft": "Pilote de l'écran ILI9341 et du tactile XPT2046",
        "module_tempo": "Couleur Tempo EDF (tâche FreeRTOS) et LED RGB clignotante",
        "module_pwm": "Sortie PWM 0-100 % sur GPIO2",
        "module_relais": "Commande du relais K1 (GPIO10)",
        "module_rfid": "Lecture des badges RC522",
        "module_bh1750": "Capteur de lumière",
        "module_bmp280": "Capteur de température et de pression",
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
